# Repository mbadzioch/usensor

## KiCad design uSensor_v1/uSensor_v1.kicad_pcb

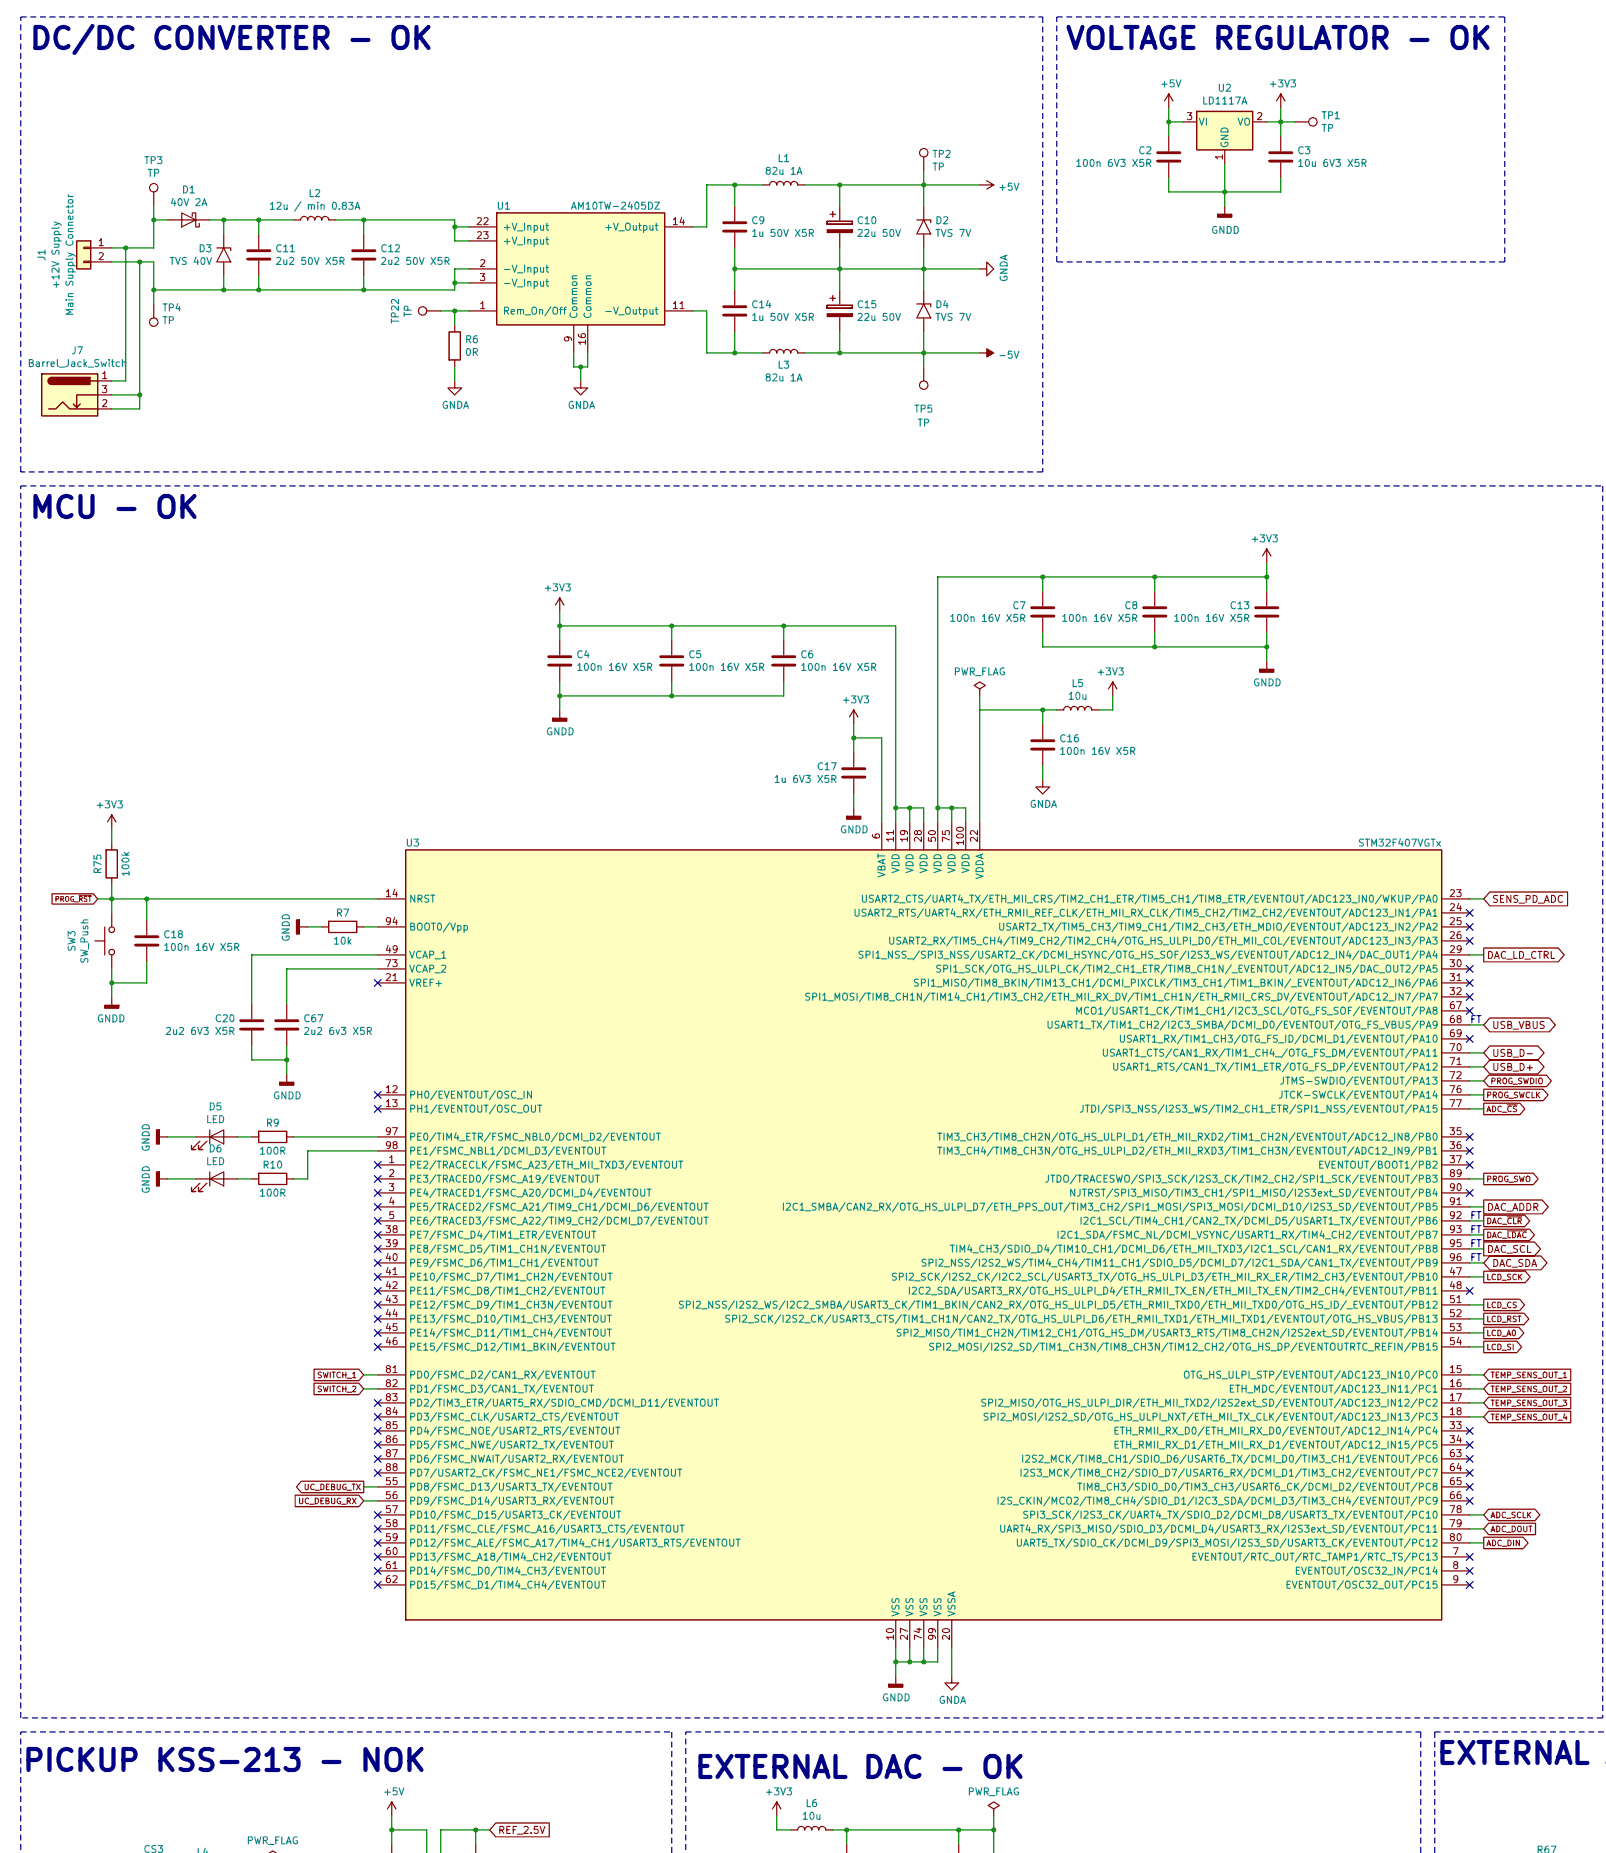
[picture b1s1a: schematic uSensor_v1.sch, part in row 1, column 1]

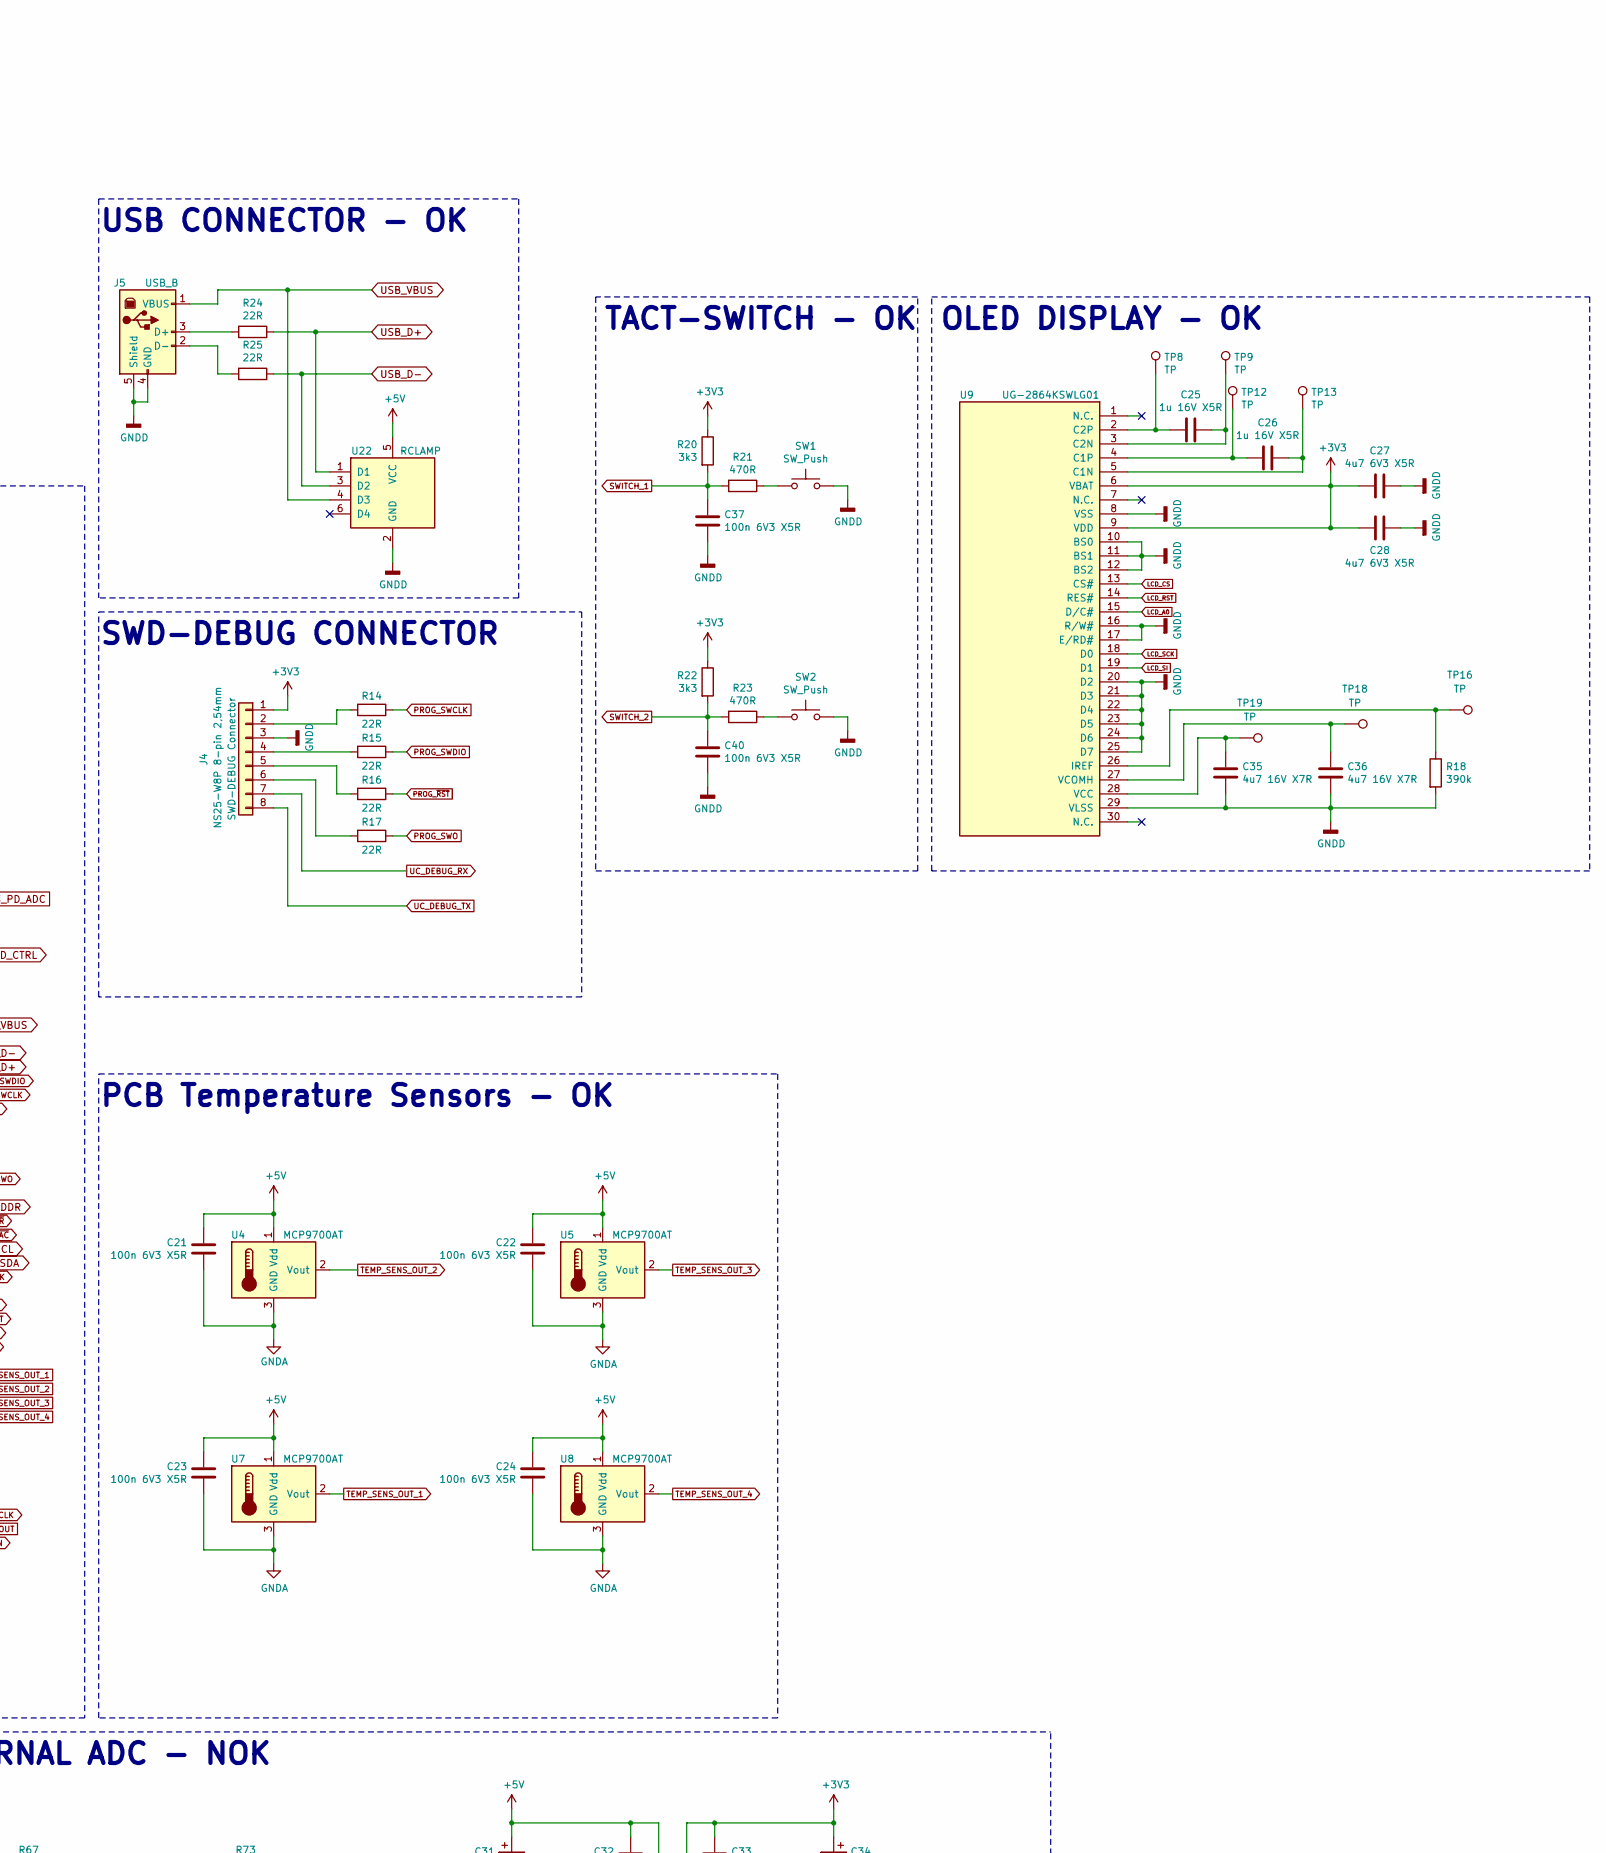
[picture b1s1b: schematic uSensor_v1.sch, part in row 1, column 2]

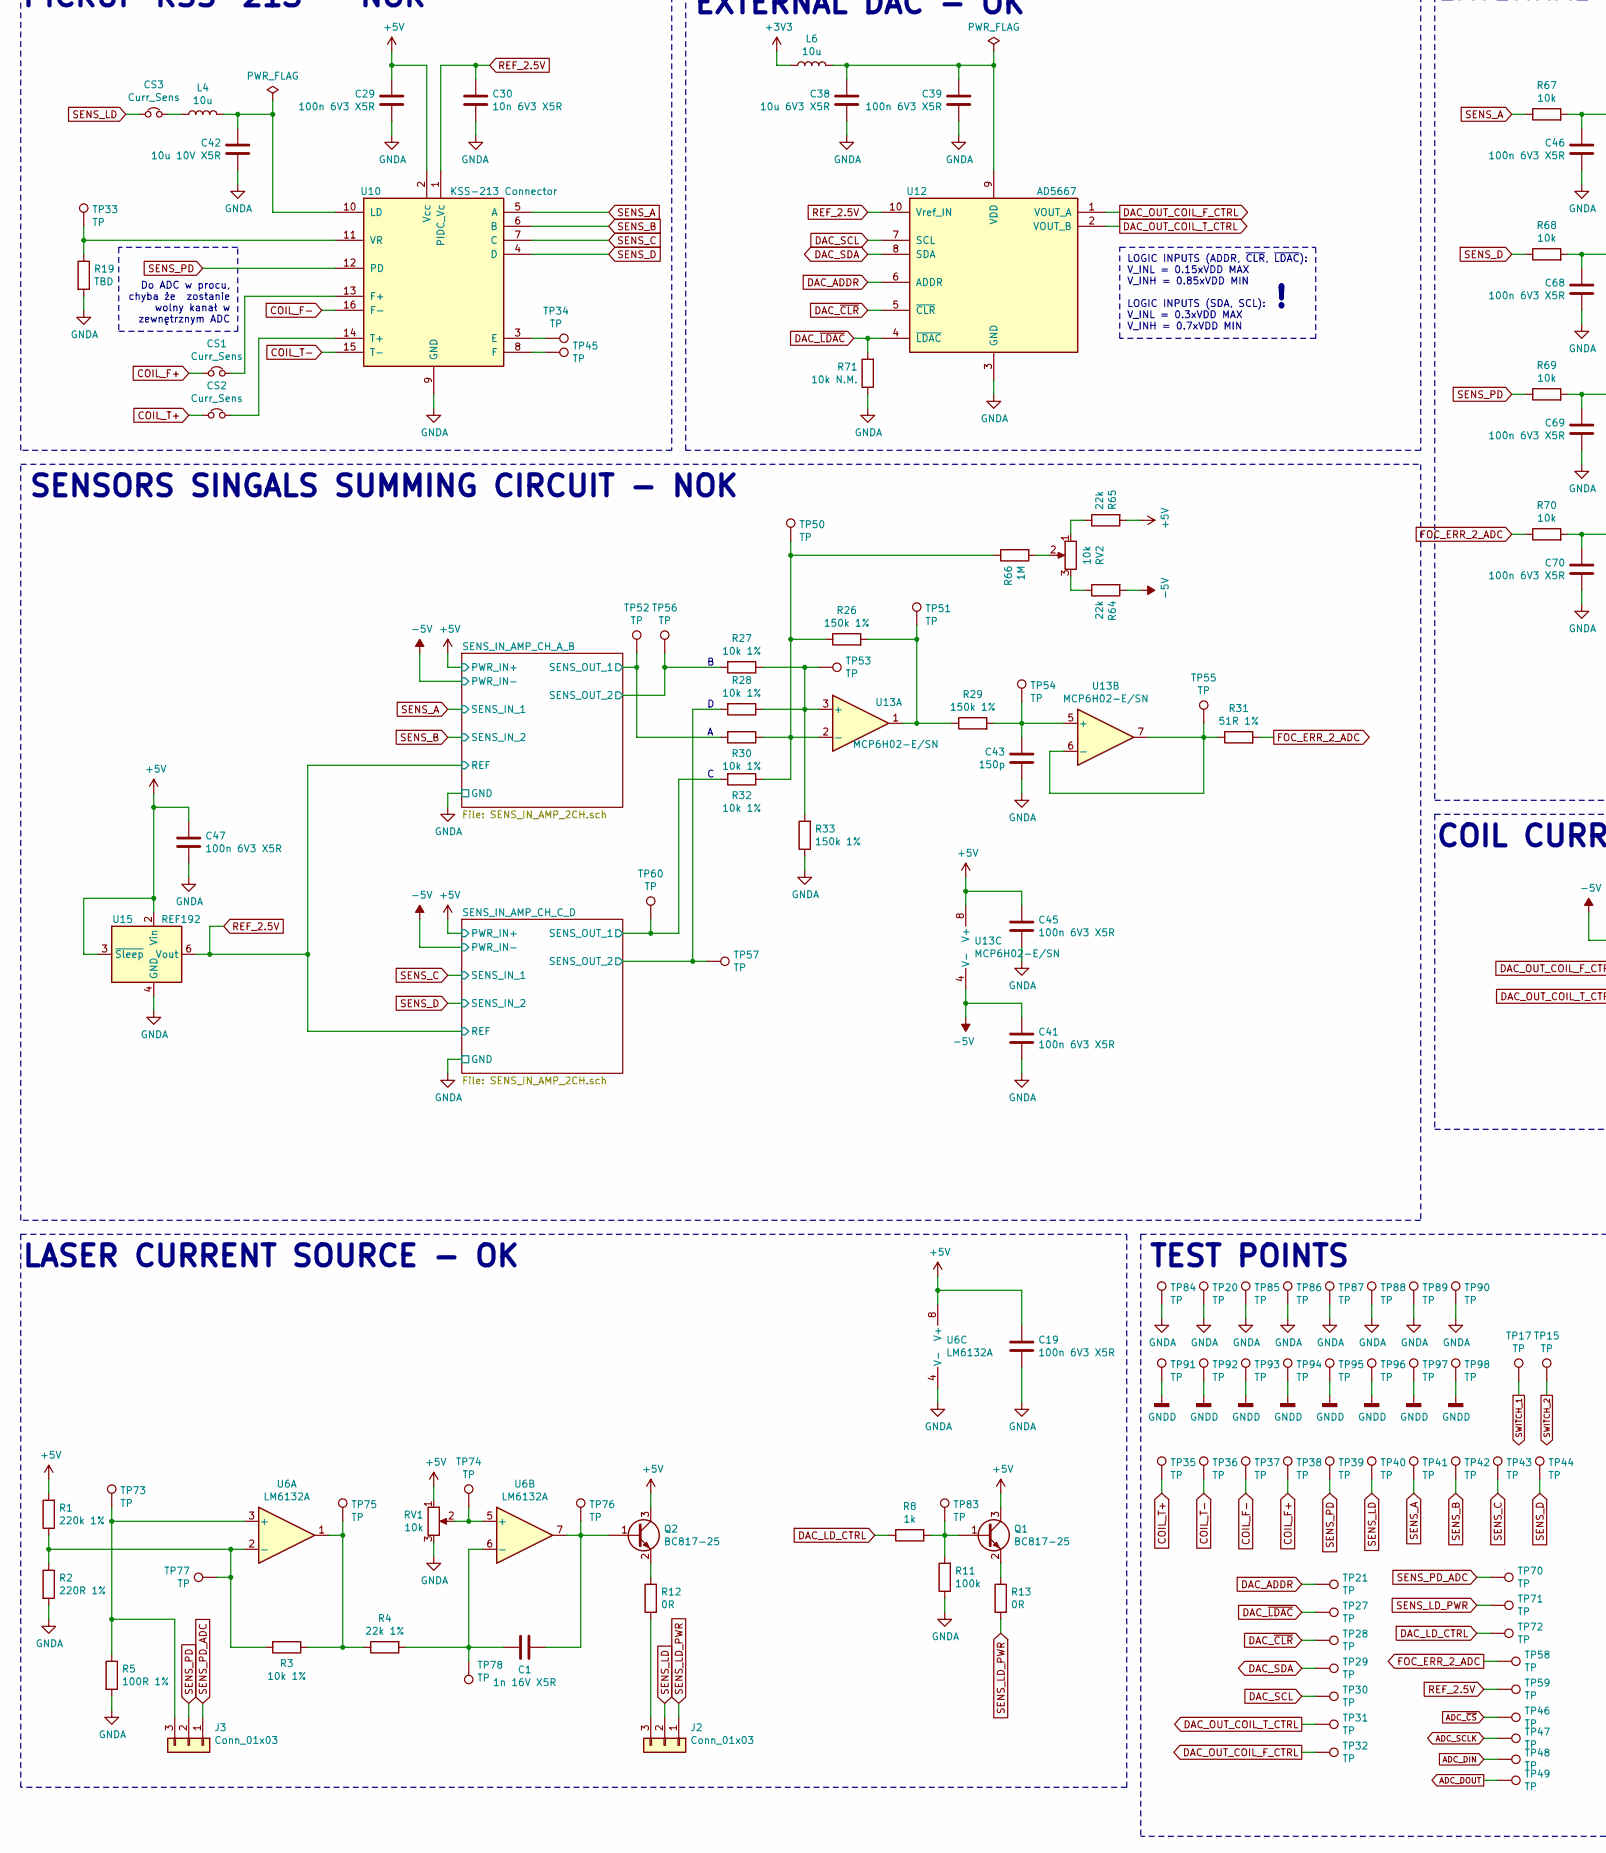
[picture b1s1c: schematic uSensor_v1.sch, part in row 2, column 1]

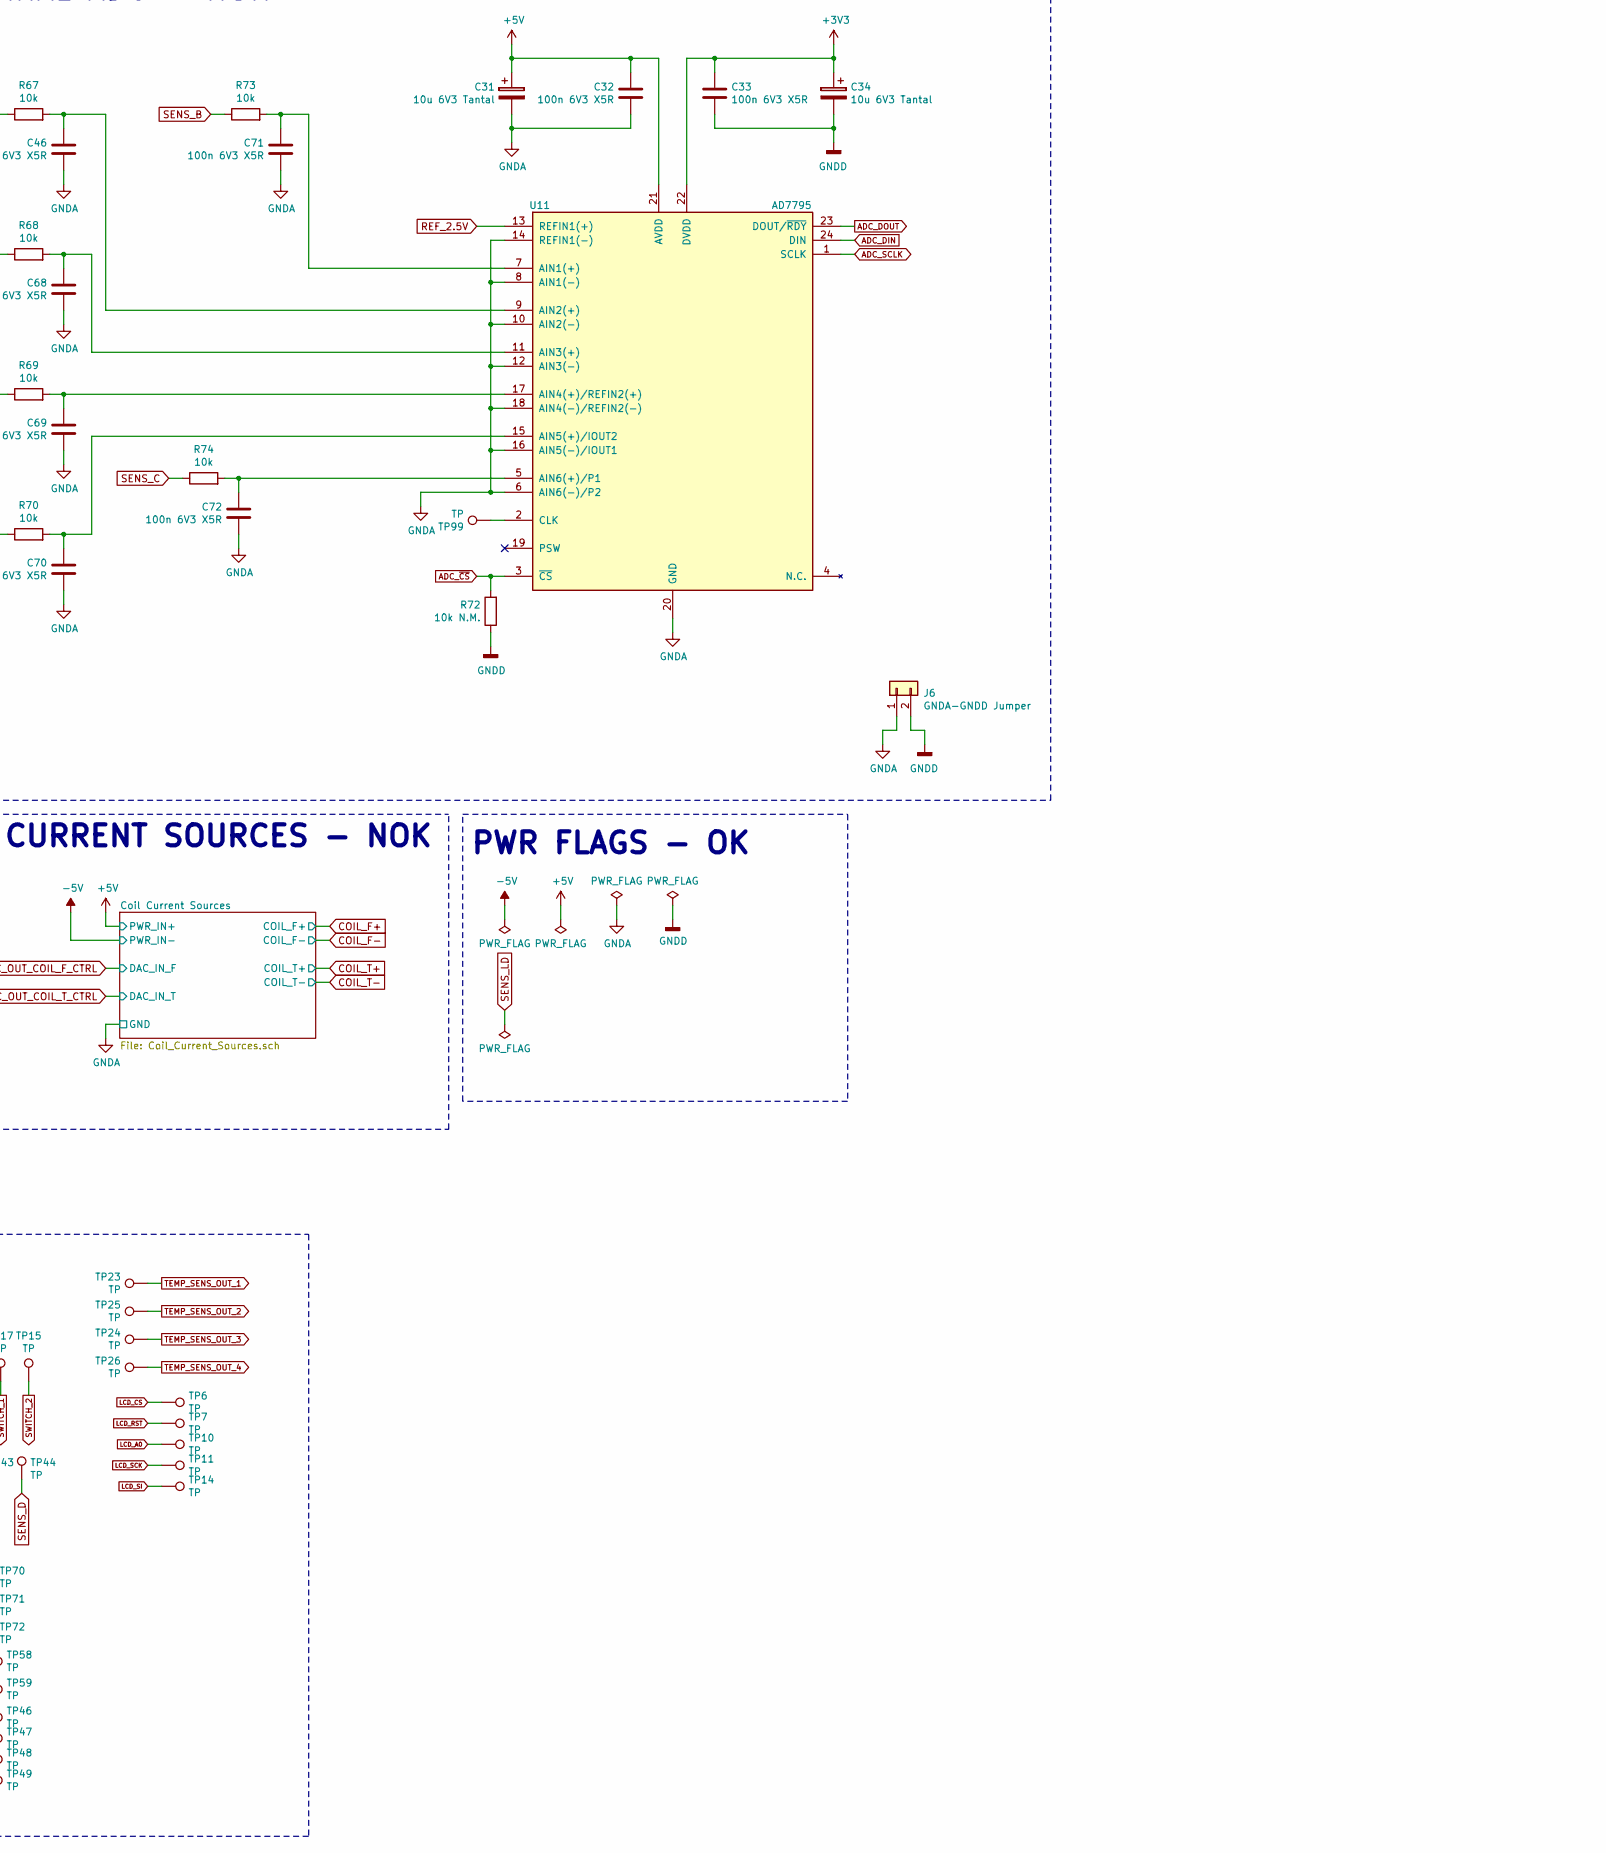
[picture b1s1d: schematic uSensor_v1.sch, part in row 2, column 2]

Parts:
C1: 1n 16V X5R; C_0603_1608Metric_Pad1.05x0.95mm_HandSolder
C2, C19, C21, C22, C23, C24, C29, C32, C33, C37, C39, C40, C41, C45, C46, C47, C68, C69, C70, C71, C72: 100n 6V3 X5R; C_0603_1608Metric_Pad1.05x0.95mm_HandSolder
C3, C38: 10u 6V3 X5R; C_0603_1608Metric_Pad1.05x0.95mm_HandSolder
C4, C5, C6, C7, C8, C13, C16, C18: 100n 16V X5R; C_0603_1608Metric_Pad1.05x0.95mm_HandSolder
C9, C14: 1u 50V X5R; C_0805_2012Metric_Pad1.15x1.40mm_HandSolder
C10, C15: 22u 50V; CP_Elec_6.3x5.3; MPN SC1H226M6L005VR
C11, C12: 2u2 50V X5R; R_0805_2012Metric_Pad1.15x1.40mm_HandSolder
C17: 1u 6V3 X5R; C_0603_1608Metric_Pad1.05x0.95mm_HandSolder
C20: 2u2 6V3 X5R; C_0603_1608Metric_Pad1.05x0.95mm_HandSolder
C25, C26: 1u 16V X5R; C_0603_1608Metric_Pad1.05x0.95mm_HandSolder
C27, C28: 4u7 6V3 X5R; C_0603_1608Metric_Pad1.05x0.95mm_HandSolder
C30: 10n 6V3 X5R; C_0603_1608Metric_Pad1.05x0.95mm_HandSolder
C31, C34: 10u 6V3 Tantal; CP_EIA-3216-10_Kemet-I_Pad1.58x1.35mm_HandSolder
C35, C36: 4u7 16V X7R; C_0603_1608Metric_Pad1.05x0.95mm_HandSolder
C42: 10u 10V X5R; C_0603_1608Metric_Pad1.05x0.95mm_HandSolder
C43: 150p; C_0603_1608Metric_Pad1.05x0.95mm_HandSolder
C67: 2u2 6v3 X5R; C_0603_1608Metric_Pad1.05x0.95mm_HandSolder
CS1, CS2, CS3: Curr_Sens; Current_Sense_Pin_Header_SMD_Pitch1.27mm
D1: 40V 2A; D_SMB; MPN SK25
D2, D4: TVS 7V; D_SMB; MPN SMBJ7.0D-M3/H
D3: TVS 40V; D_SMB; MPN Vishay
D5, D6: LED; LED_0603_1608Metric_Pad1.05x0.95mm_HandSolder
J1: +12V Supply; Molex_KK-254_AE-6410-02A_1x02_P2.54mm_Vertical
J2, J3: Conn_01x03; PinHeader_1x03_P2.54mm_Vertical
J4: NS25-W8P 8-pin 2,54mm; Molex_KK-254_AE-6410-08A_1x08_P2.54mm_Vertical; MPN NS25-W8P
J5: USB_B; USB_B_OST_USB-B1HSxx_Horizontal
J6: GNDA-GNDD Jumper; PinHeader_1x02_P2.54mm_Vertical
J7: Barrel_Jack_Switch; BarrelJack_Wuerth_6941xx301002; MPN FC681465P
L1, L3: 82u 1A; L_1210_3225Metric_Pad1.42x2.65mm_HandSolder; MPN 1210AS-082J-01
L2: 12u / min 0.83A; FERROCORE_DLG-0705-120; MPN DLG-0705-120
L4: 10u; L_1210_3225Metric_Pad1.42x2.65mm_HandSolder; MPN NLCV32T-100K-EF
L5, L6: 10u; L_1210_3225Metric_Pad1.42x2.65mm_HandSolder
Q1, Q2: BC817-25; SOT-23_o1; MPN BC817-25
R1: 220k 1%; R_0603_1608Metric_Pad1.05x0.95mm_HandSolder
R2: 220R 1%; R_0603_1608Metric_Pad1.05x0.95mm_HandSolder
R3, R27, R28, R30, R32: 10k 1%; R_0603_1608Metric_Pad1.05x0.95mm_HandSolder
R4: 22k 1%; R_0603_1608Metric_Pad1.05x0.95mm_HandSolder
R5: 100R 1%; R_0603_1608Metric_Pad1.05x0.95mm_HandSolder
R6: 0R; R_0603_1608Metric_Pad1.05x0.95mm_HandSolder
R7, R67, R68, R69, R70, R73, R74: 10k; R_0603_1608Metric_Pad1.05x0.95mm_HandSolder
R8: 1k; R_0603_1608Metric_Pad1.05x0.95mm_HandSolder
R9, R10: 100R; R_0603_1608Metric_Pad1.05x0.95mm_HandSolder
R11, R75: 100k; R_0603_1608Metric_Pad1.05x0.95mm_HandSolder
R12, R13: 0R; R_1206
R14, R15, R16, R17, R24, R25: 22R; R_0603_1608Metric_Pad1.05x0.95mm_HandSolder
R18: 390k; R_0603_1608Metric_Pad1.05x0.95mm_HandSolder
R19: TBD; R_0603
R20, R22: 3k3; R_0603_1608Metric_Pad1.05x0.95mm_HandSolder
R21, R23: 470R; R_0603_1608Metric_Pad1.05x0.95mm_HandSolder
R26, R29, R33: 150k 1%; R_0603_1608Metric_Pad1.05x0.95mm_HandSolder
R31: 51R 1%; R_0603_1608Metric_Pad1.05x0.95mm_HandSolder
R64, R65: 22k; R_0603_1608Metric_Pad1.05x0.95mm_HandSolder
R66: 1M; R_0603_1608Metric_Pad1.05x0.95mm_HandSolder
R71, R72: 10k N.M.; R_0603_1608Metric_Pad1.05x0.95mm_HandSolder
RV1, RV2: 10k; Potentiometer_SR_Passives_T910W_Vertical; MPN T910W-10K
SW1, SW2, SW3: SW_Push; SW_PUSH_6mm_H4.3mm; MPN TACT-67N-F
TP1, TP2, TP3, TP4, TP5, TP6, TP7, TP8, TP9, TP10, TP11, TP12, TP13, TP14, TP15, TP16, TP17, TP18, TP19, TP20, TP21, TP22, TP23, TP24, TP25, TP26, TP27, TP28, TP29, TP30, TP31, TP32, TP33, TP34, TP35, TP36, TP37, TP38, TP39, TP40, TP41, TP42, TP43, TP44, TP45, TP46, TP47, TP48, TP49, TP50, TP51, TP52, TP53, TP54, TP55, TP56, TP57, TP58, TP59, TP60, TP70, TP71, TP72, TP73, TP74, TP75, TP76, TP77, TP78, TP83, TP84, TP85, TP86, TP87, TP88, TP89, TP90, TP91, TP92, TP93, TP94, TP95, TP96, TP97, TP98, TP99: TP; TestPoint_Probe_1.0mmDiameter_0.6mmDrill
U1: AM10TW-2405DZ; AIMTEC_AM10TW-2405DZ
U2: LD1117A; TO-252-2; MPN LD1117ADT33TR
U3: STM32F407VGTx; ST_S-LQFP-100_14x14mm_P0.5mm
U4, U5, U7, U8: MCP9700AT; SOT-23; MPN MCP9700AT-E/TT
U6: LM6132A; SO-8; MPN LM6132AIM/NOPB
U9: UG-2864KSWLG01; UG-2864KSWLG01_Adhessive_Tape_Flat_Mounting; MPN UG-2864KSWLG01
U10: KSS-213 Connector; Molex_52271-1679_1x16_1mm_Pitch_FFC_FPC_Horizontal_SMT; MPN (TDB) KSS-213C
U11: AD7795; TSSOP-24_4.4x7.8mm_Pitch0.65mm; MPN AD7795BRUZ
U12: AD5667; MSOP-10_4.9x3.0mm_Pitch0.5mm; MPN AD5667BRMZ
U13: MCP6H02-E/SN; SO-8; MPN MCP6H02-E/SN
U15: REF192; SO-8; MPN REF192FSZ
U22: RCLAMP; SOT-23-6; MPN RCLAMP0504S.TCT

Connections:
+3V3: C3.1, C4.1, C5.1, C6.1, C7.1, C8.1, C13.1, C17.1, C27.2, C28.2, C33.1, C34.1, J4.1, L5.2, L6.1, R20.1, R22.1, R75.2, TP1.1, U2.2 (VO), U3.6 (VBAT), U3.11 (VDD), U3.19 (VDD), U3.28 (VDD), U3.50 (VDD), U3.75 (VDD), U3.100 (VDD), U9.6 (VBAT), U9.9 (VDD), U11.22 (DVDD)
-5V: C15.2, C41.1, D4.2 (A2), L3.2, R64.2, TP5.1, U13.4 (V-); also elsewhere on the board
/SENS_IN_AMP_CH_C_D/SENS_OUT_1: R32.2, TP60.1; also elsewhere on the board
/SENS_IN_AMP_CH_C_D/SENS_OUT_2: R28.2, TP57.1; also elsewhere on the board
ADC_DIN: TP48.1, U3.80 (UART5_TX/SDIO_CK/DCMI_D9/SPI3_MOSI/I2S3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), U11.24 (DIN)
ADC_DOUT: TP49.1, U3.79 (UART4_RX/SPI3_MISO/SDIO_D3/DCMI_D4/USAR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), U11.23 (DOUT/~RDY)
ADC_SCLK: TP47.1, U3.78 (SPI3_SCK/I2S3_CK/UART4_TX/SDIO_D2/DCMI_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), U11.1 (SCLK)
ADC_~CS: R72.2, TP46.1, U3.77 (JTDI/SPI3_NSS/I2S3_WS/TIM2_CH1_ETR/SPI1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), U11.3 (~CS)
COIL_F+: CS1.1, TP38.1; also elsewhere on the board
COIL_F-: TP37.1, U10.16 (F-); also elsewhere on the board
COIL_T+: CS2.1, TP35.1; also elsewhere on the board
COIL_T-: TP36.1, U10.15 (T-); also elsewhere on the board
DAC_ADDR: TP21.1, U3.91 (I2C1_SMBA/CAN2_RX/OTG_HS_ULPI_D7/ETH_PP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), U12.6 (ADDR)
DAC_LD_CTRL: R8.2, TP72.1, U3.29 (SPI1_NSS_/SPI3_NSS/USART2_CK/DCMI_HSYNC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)
DAC_OUT_COIL_F_CTRL: TP32.1, U12.1 (VOUT_A); also elsewhere on the board
DAC_OUT_COIL_T_CTRL: TP31.1, U12.2 (VOUT_B); also elsewhere on the board
DAC_SCL: TP30.1, U3.95 (TIM4_CH3/SDIO_D4/TIM10_CH1/DCMI_D6/ETH_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), U12.7 (SCL)
DAC_SDA: TP29.1, U3.96 (SPI2_NSS/I2S2_WS/TIM4_CH4/TIM11_CH1/SDI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), U12.8 (SDA)
DAC_~CLR: TP28.1, U3.92 (I2C1_SCL/TIM4_CH1/CAN2_TX/DCMI_D5/USART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), U12.5 (~CLR)
DAC_~LDAC: R71.2, TP27.1, U3.93 (I2C1_SDA/FSMC_NL/DCMI_VSYNC/USART1_RX/T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), U12.4 (~LDAC)
FOC_ERR_2_ADC: R31.2, R70.1, TP58.1
GNDD: C2.2, C3.2, C4.2, C5.2, C6.2, C7.2, C8.2, C13.2, C17.2, C18.2, C20.2, C27.1, C28.1, C33.2, C34.2, C35.2, C36.2, C37.2, C40.2, C67.2, D5.1 (K), D6.1 (K), J4.3, J5.4 (GND), J5.5 (Shield), J6.2, R7.2, R18.2, R72.1, SW1.2, SW2.2, SW3.2, TP91.1, TP92.1, TP93.1, TP94.1, TP95.1, TP96.1, TP97.1, TP98.1, U2.1 (GND), U3.10 (VSS), U3.27 (VSS), U3.74 (VSS), U3.99 (VSS), U9.8 (VSS), U9.10 (BS0), U9.11 (BS1), U9.12 (BS2), U9.16 (R/W#), U9.17 (E/RD#), U9.20 (D2), U9.21 (D3), U9.22 (D4), U9.23 (D5), U9.24 (D6), U9.25 (D7), U9.29 (VLSS), U22.2 (GND)
LCD_A0: TP10.1, U3.53 (SPI2_MISO/TIM1_CH2N/TIM12_CH1/OTG_HS_DM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), U9.15 (D/C#)
LCD_CS: TP6.1, U3.51 (SPI2_NSS/I2S2_WS/I2C2_SMBA/USART3_CK/TI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), U9.13 (CS#)
LCD_RST: TP7.1, U3.52 (SPI2_SCK/I2S2_CK/USART3_CTS/TIM1_CH1N/C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), U9.14 (RES#)
LCD_SCK: TP11.1, U3.47 (SPI2_SCK/I2S2_CK/I2C2_SCL/USART3_TX/OTG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), U9.18 (D0)
LCD_SI: TP14.1, U3.54 (SPI2_MOSI/I2S2_SD/TIM1_CH3N/TIM8_CH3N/T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), U9.19 (D1)
unnamed: C1.1, Q2.1 (B), TP76.1, U6.7
unnamed: C1.2, R4.2, TP78.1, U6.6 (-)
unnamed: C9.1, L1.1, U1.14 (+V_Output)
unnamed: C11.1, D1.1 (K), D3.1 (A1), L2.1
unnamed: C11.2, C12.2, D3.2 (A2), J1.2, J7.2, J7.3, TP4.1, U1.2 (-V_Input), U1.3 (-V_Input)
unnamed: C12.1, L2.2, U1.22 (+V_Input), U1.23 (+V_Input)
unnamed: C14.2, L3.1, U1.11 (-V_Output)
unnamed: C16.1, L5.1, U3.22 (VDDA)
unnamed: C20.1, U3.49 (VCAP_1)
unnamed: C25.1, TP9.1, U9.3 (C2N)
unnamed: C25.2, TP8.1, U9.2 (C2P)
unnamed: C26.1, TP13.1, U9.5 (C1N)
unnamed: C26.2, TP12.1, U9.4 (C1P)
unnamed: C35.1, TP19.1, U9.28 (VCC)
unnamed: C36.1, TP18.1, U9.27 (VCOMH)
unnamed: C38.1, C39.1, L6.2, U12.9 (VDD)
unnamed: C42.1, L4.2, U10.10 (LD)
unnamed: C43.2, R29.2, TP54.1, U13.5 (+)
unnamed: C46.1, R67.2, U11.9 (AIN2(+))
unnamed: C67.1, U3.73 (VCAP_2)
unnamed: C68.1, R68.2, U11.11 (AIN3(+))
unnamed: C69.1, R69.2, U11.17 (AIN4(+)/REFIN2(+))
unnamed: C70.1, R70.2, U11.15 (AIN5(+)/IOUT2)
unnamed: C71.1, R73.2, U11.7 (AIN1(+))
unnamed: C72.1, R74.2, U11.5 (AIN6(+)/P1)
unnamed: CS1.2, U10.13 (F+)
unnamed: CS2.2, U10.14 (T+)
unnamed: CS3.2, L4.1
unnamed: D1.2 (A), J1.1, J7.1, TP3.1
unnamed: D5.2 (A), R9.2
unnamed: D6.2 (A), R10.2
unnamed: J2.3, R12.2
unnamed: J3.3, R5.1, TP73.1, U6.3 (+)
unnamed: J4.2, R14.2
unnamed: J4.4, R15.2
unnamed: J4.5, R16.2
unnamed: J4.6, R17.2
unnamed: J5.2 (D-), R25.2
unnamed: J5.3 (D+), R24.2
unnamed: Q1.1 (B), R8.1, R11.2, TP83.1
unnamed: Q1.2 (E), R13.1
unnamed: Q2.2 (E), R12.1
unnamed: R1.1, R2.1, R3.2, TP77.1, U6.2 (-)
unnamed: R3.1, R4.1, TP75.1, U6.1
unnamed: R6.1, TP22.1, U1.1 (Rem_On/Off)
unnamed: R7.1, U3.94 (BOOT0/Vpp)
unnamed: R9.1, U3.97 (PE0/TIM4_ETR/FSMC_NBL0/DCMI_D2/EVENTOUT)
unnamed: R10.1, U3.98 (PE1/FSMC_NBL1/DCMI_D3/EVENTOUT)
unnamed: R18.1, TP16.1, U9.26 (IREF)
unnamed: R19.1, TP33.1, U10.11 (VR)
unnamed: R21.1, SW1.1
unnamed: R23.1, SW2.1
unnamed: R26.1, R30.1, R32.1, R66.1, TP50.1, U13.2 (-)
unnamed: R26.2, R29.1, TP51.1, U13.1
unnamed: R27.1, R28.1, R33.2, TP53.1, U13.3 (+)
unnamed: R31.1, TP55.1, U13.6 (-), U13.7
unnamed: R64.1, RV2.3
unnamed: R65.1, RV2.1
unnamed: R66.2, RV2.2
unnamed: RV1.2, TP74.1, U6.5 (+)
unnamed: TP34.1, U10.3 (E)
unnamed: TP45.1, U10.8 (F)
unnamed: TP99.1, U11.2 (CLK)
PROG_SWCLK: R14.1, U3.76 (JTCK-SWCLK/EVENTOUT/PA14)
PROG_SWDIO: R15.1, U3.72 (JTMS-SWDIO/EVENTOUT/PA13)
PROG_SWO: R17.1, U3.89 (JTDO/TRACESWO/SPI3_SCK/I2S3_CK/TIM2_CH2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)
PROG_~RST: C18.1, R16.1, R75.1, SW3.1, U3.14 (NRST)
SENS_C: R74.1, TP43.1, U10.7 (C); also elsewhere on the board
SENS_D: R68.1, TP44.1, U10.4 (D); also elsewhere on the board
SENS_LD: CS3.1, J2.2, TP40.1
SENS_LD_PWR: J2.1, R13.2, TP71.1
SENS_PD: J3.2, R69.1, TP39.1, U10.12 (PD)
SENS_PD_ADC: J3.1, TP70.1, U3.23 (USART2_CTS/UART4_TX/ETH_MII_CRS/TIM2_CH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)
SWITCH_1: C37.1, R20.2, R21.2, TP17.1, U3.81 (PD0/FSMC_D2/CAN1_RX/EVENTOUT)
SWITCH_2: C40.1, R22.2, R23.2, TP15.1, U3.82 (PD1/FSMC_D3/CAN1_TX/EVENTOUT)
TEMP_SENS_OUT_1: TP23.1, U3.15 (OTG_HS_ULPI_STP/EVENTOUT/ADC123_IN10/PC0), U7.2 (Vout)
TEMP_SENS_OUT_2: TP25.1, U3.16 (ETH_MDC/EVENTOUT/ADC123_IN11/PC1), U4.2 (Vout)
TEMP_SENS_OUT_3: TP24.1, U3.17 (SPI2_MISO/OTG_HS_ULPI_DIR/ETH_MII_TXD2/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), U5.2 (Vout)
TEMP_SENS_OUT_4: TP26.1, U3.18 (SPI2_MOSI/I2S2_SD/OTG_HS_ULPI_NXT/ETH_M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), U8.2 (Vout)
UC_DEBUG_RX: J4.7, U3.56 (PD9/FSMC_D14/USART3_RX/EVENTOUT)
UC_DEBUG_TX: J4.8, U3.55 (PD8/FSMC_D13/USART3_TX/EVENTOUT)
USB_D+: R24.1, U3.71 (USART1_RTS/CAN1_TX/TIM1_ETR/OTG_FS_DP/E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), U22.1 (D1)
USB_D-: R25.1, U3.70 (USART1_CTS/CAN1_RX/TIM1_CH4_/OTG_FS_DM/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), U22.3 (D2)
USB_VBUS: J5.1 (VBUS), U3.68 (USART1_TX/TIM1_CH2/I2C3_SMBA/DCMI_D0/EV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), U22.4 (D3)

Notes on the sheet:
OLED DISPLAY - OK
TACT-SWITCH - OK
LASER CURRENT SOURCE - OK
COIL CURRENT SOURCES - NOK
PICKUP KSS-213 - NOK
PCB Temperature Sensors - OK
DC/DC CONVERTER - OK
SENSORS SINGALS SUMMING CIRCUIT - NOK
EXTERNAL DAC - OK
EXTERNAL ADC - NOK
USB CONNECTOR - OK
SWD-DEBUG CONNECTOR
MCU - OK
VOLTAGE REGULATOR - OK
PWR FLAGS - OK
LOGIC INPUTS (ADDR, ~CLR~, ~LDAC~): V_INL = 0.15xVDD MAX V_INH = 0.85xVDD MIN LOGIC INPUTS (SDA, SCL): V_INL = 0.3xVDD MAX V_INH = 0.7xVDD MIN
TEST POINTS
Do ADC w procu, chyba że zostanie wolny kanał w zewnętrznym ADC

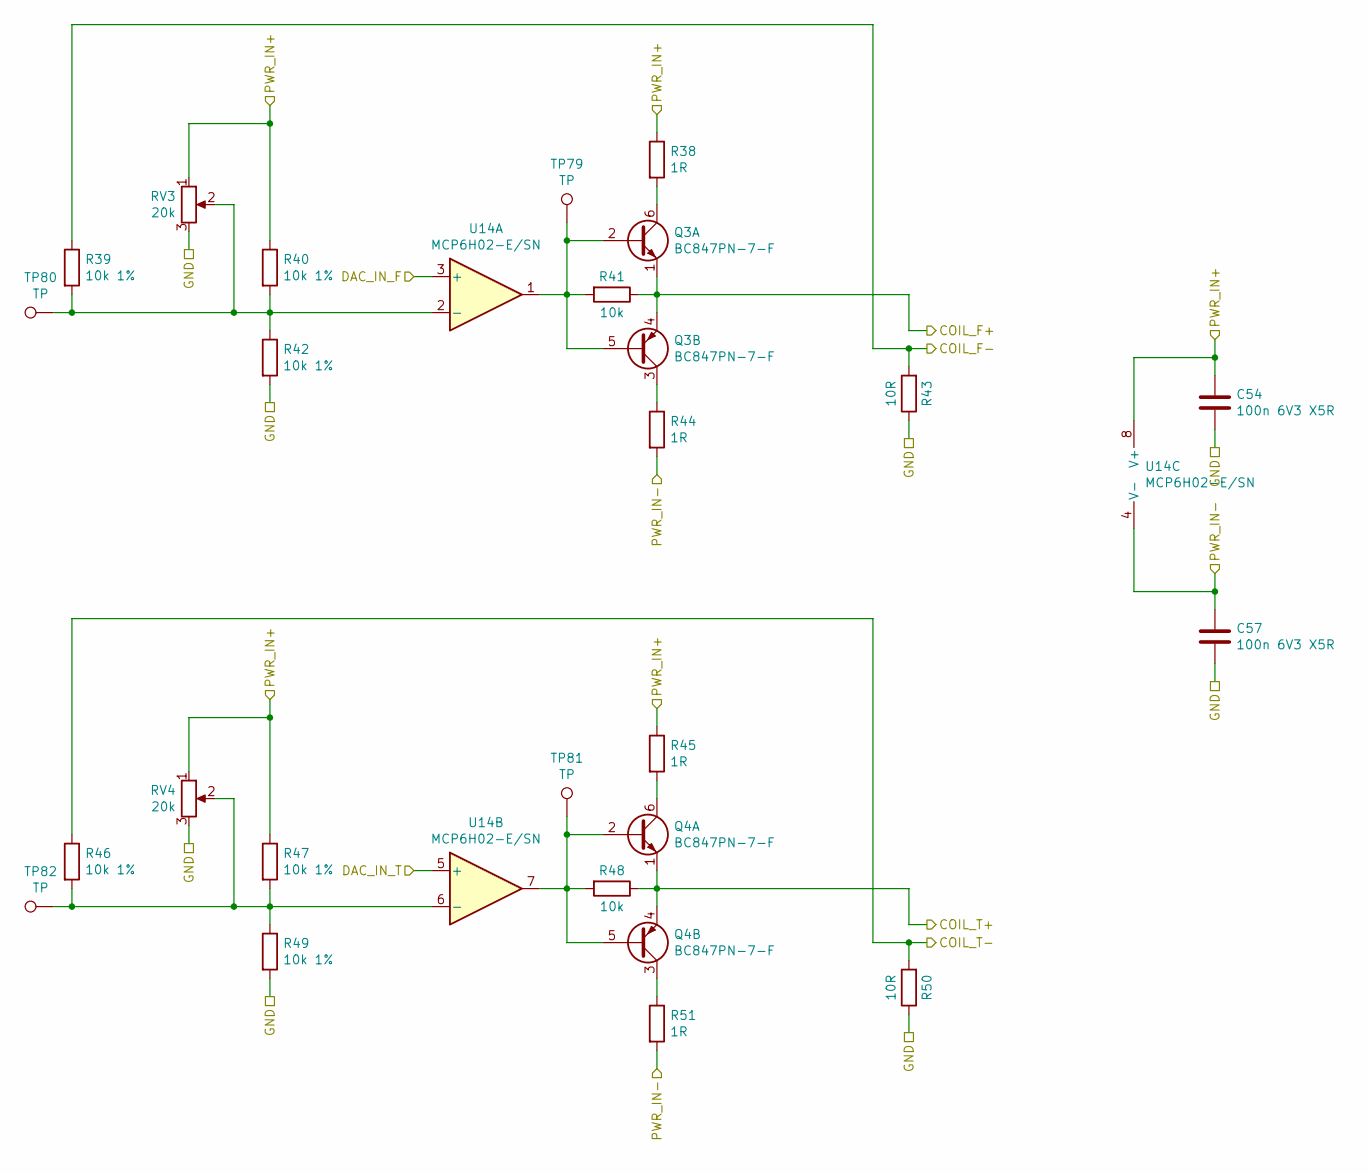
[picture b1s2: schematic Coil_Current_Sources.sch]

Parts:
C54, C57: 100n 6V3 X5R; C_0603_1608Metric_Pad1.05x0.95mm_HandSolder
Q3, Q4: BC847PN-7-F; SOT-363; MPN BC847PN-7-F
R38, R44, R45, R51: 1R; R_0603_1608Metric_Pad1.05x0.95mm_HandSolder
R39, R40, R42, R46, R47, R49: 10k 1%; R_0603_1608Metric_Pad1.05x0.95mm_HandSolder
R41, R48: 10k; R_0603_1608Metric_Pad1.05x0.95mm_HandSolder
R43, R50: 10R; R_0603_1608Metric_Pad1.05x0.95mm_HandSolder
RV3, RV4: 20k; Potentiometer_SR_Passives_T910W_Vertical; MPN T910W-20K
TP79, TP80, TP81, TP82: TP; TestPoint_Probe_1.0mmDiameter_0.6mmDrill
U14: MCP6H02-E/SN; SO-8; MPN MCP6H02-E/SN

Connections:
-5V: C57.1, R44.2, R51.2, U14.4 (V-); also elsewhere on the board
COIL_F+: Q3.1 (E1), Q3.4 (E2), R41.1; also elsewhere on the board
COIL_F-: R39.1, R43.2; also elsewhere on the board
COIL_T+: Q4.1 (E1), Q4.4 (E2), R48.1; also elsewhere on the board
COIL_T-: R46.1, R50.2; also elsewhere on the board
DAC_OUT_COIL_F_CTRL: U14.3 (+); also elsewhere on the board
DAC_OUT_COIL_T_CTRL: U14.5 (+); also elsewhere on the board
unnamed: Q3.2 (B1), Q3.5 (B2), R41.2, TP79.1, U14.1
unnamed: Q3.3 (C2), R44.1
unnamed: Q3.6 (C1), R38.2
unnamed: Q4.2 (B1), Q4.5 (B2), R48.2, TP81.1, U14.7
unnamed: Q4.3 (C2), R51.1
unnamed: Q4.6 (C1), R45.2
unnamed: R39.2, R40.2, R42.1, RV3.2, TP80.1, U14.2 (-)
unnamed: R46.2, R47.2, R49.1, RV4.2, TP82.1, U14.6 (-)

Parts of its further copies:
C56: 100n 6V3 X5R; C_0603_1608Metric_Pad1.05x0.95mm_HandSolder

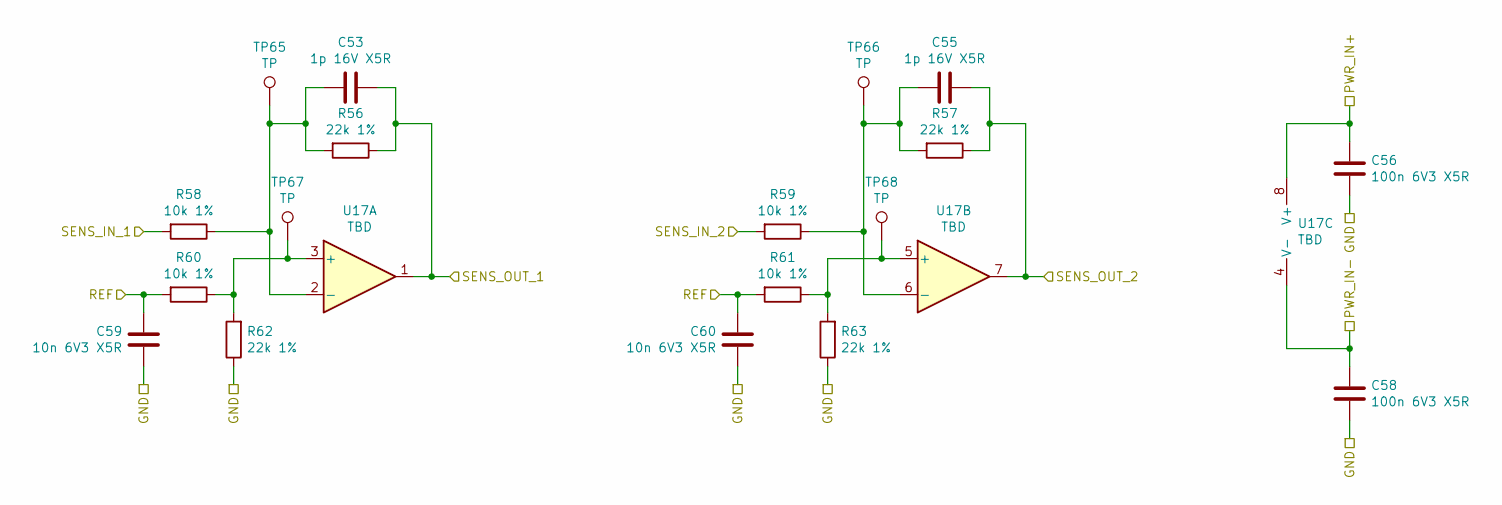
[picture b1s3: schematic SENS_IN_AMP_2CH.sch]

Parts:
C50, C51: 1p 16V X5R; C_0603_1608Metric_Pad1.05x0.95mm_HandSolder
C52: 100n 6V3 X5R; C_0603_1608Metric_Pad1.05x0.95mm_HandSolder
C59, C60: 10n 6V3 X5R; C_0603_1608Metric_Pad1.05x0.95mm_HandSolder
R34, R37, R55: 22k 1%; R_0603_1608Metric_Pad1.05x0.95mm_HandSolder
R35, R36, R53: 10k 1%; R_0603_1608Metric_Pad1.05x0.95mm_HandSolder
TP62, TP64, TP66, TP67: TP; TestPoint_Probe_1.0mmDiameter_0.6mmDrill
U16: TBD; SO-8; MPN TBD

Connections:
-5V: C52.1, U16.4 (V-); also elsewhere on the board
unnamed: R53.1, R55.2, TP64.1, U16.5 (+)

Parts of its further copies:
C44, C48: 10n 6V3 X5R; C_0603_1608Metric_Pad1.05x0.95mm_HandSolder
C49, C53, C55, C61, C64: 1p 16V X5R; C_0603_1608Metric_Pad1.05x0.95mm_HandSolder
C58: 100n 6V3 X5R; C_0603_1608Metric_Pad1.05x0.95mm_HandSolder
R54, R56, R62, R63: 22k 1%; R_0603_1608Metric_Pad1.05x0.95mm_HandSolder
R58, R61: 10k 1%; R_0603_1608Metric_Pad1.05x0.95mm_HandSolder
TP61, TP63, TP65, TP68, TP69: TP; TestPoint_Probe_1.0mmDiameter_0.6mmDrill

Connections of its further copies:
-5V: C58.1; also elsewhere on the board
/SENS_IN_AMP_CH_C_D/SENS_OUT_1: C53.1, R56.1; also elsewhere on the board
/SENS_IN_AMP_CH_C_D/SENS_OUT_2: C55.1; also elsewhere on the board
unnamed 46: C53.2, R56.2, R58.1, TP65.1; also elsewhere on the board
unnamed 93: R61.1, R63.2, TP68.1; also elsewhere on the board
SENS_C: R58.2; also elsewhere on the board

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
